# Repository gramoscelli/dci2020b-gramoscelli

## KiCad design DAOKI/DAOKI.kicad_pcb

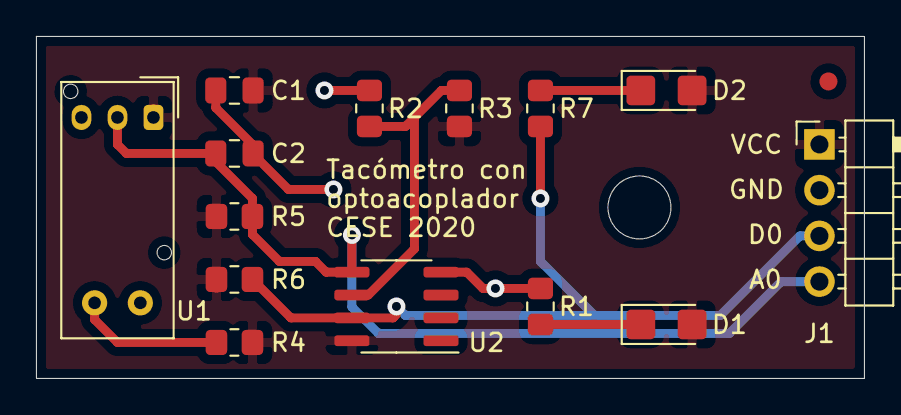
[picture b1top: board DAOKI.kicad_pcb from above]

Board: 2 copper layers, 46.0 x 19.0 mm, 16 parts (0 on the bottom side), 8 nets.

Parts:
C1, C2: 100nF; C_0805_2012Metric_Pad1.18x1.45mm_HandSolder
D1: LED POWER; LED_1206_3216Metric_Castellated
D2: LED SWITCH; LED_1206_3216Metric_Castellated
FID1: Fiducial; Fiducial_1mm_Mask2mm
H1: Mounting Hole; MountingHole_4.3mm_M4
J1: CON1; PinHeader_1x04_P2.54mm_Horizontal
R1, R7: 1K; R_0805_2012Metric_Pad1.20x1.40mm_HandSolder
R2, R3, R5, R6: 10K; R_0805_2012Metric_Pad1.20x1.40mm_HandSolder
R4: 100; R_0805_2012Metric_Pad1.20x1.40mm_HandSolder
U1: LG206D; Kodenshi_LG206D
U2: LM393; SOIC-8_3.9x4.9mm_P1.27mm

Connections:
+5V: C1.1, D1.2, D2.2, J1.1, R3.1, R4.1, R5.1, R6.1, U1.1, U2.8
GND: C1.2, C2.2, J1.2, R1.2, R2.2, U1.3, U1.5, U2.4
unnamed: C2.1, J1.4, R5.2, U1.2, U2.5
unnamed: D1.1, R1.1
unnamed: D2.1, R7.1
unnamed: J1.3, R6.2, R7.2, U2.7
unnamed: R2.1, R3.2, U2.6
unnamed: R4.2, U1.4

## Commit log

2020-10-28 First commit!
2020-10-28 add some manuals
2020-11-07 adding PCB
2020-11-07 Add 3d model of one component
2020-11-09 New routing
2020-11-09 add photo with dimensions
2020-11-09 change some vias drill size
2020-11-11 Some schematic improvements
2020-11-16 Some fixies on PCB file
2020-11-18 add PCB notes
2020-11-18 add optointerrupter local manual
2020-11-18 final fixies on notes to PCB maker

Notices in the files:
DAOKI/DAOKI.kicad_pcb:
All rights reserved
Copyright (c) 2020, Gustavo Ramoscelli, BSD Clausule-3 License
